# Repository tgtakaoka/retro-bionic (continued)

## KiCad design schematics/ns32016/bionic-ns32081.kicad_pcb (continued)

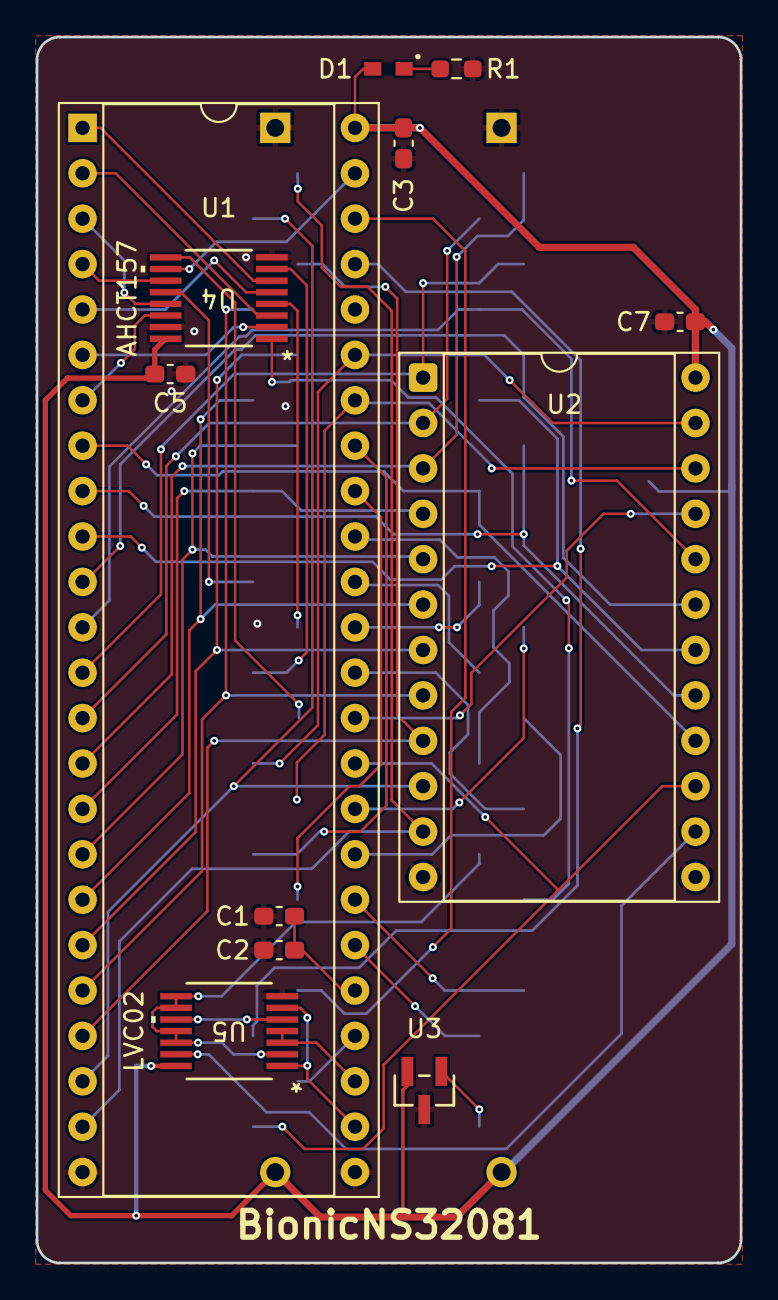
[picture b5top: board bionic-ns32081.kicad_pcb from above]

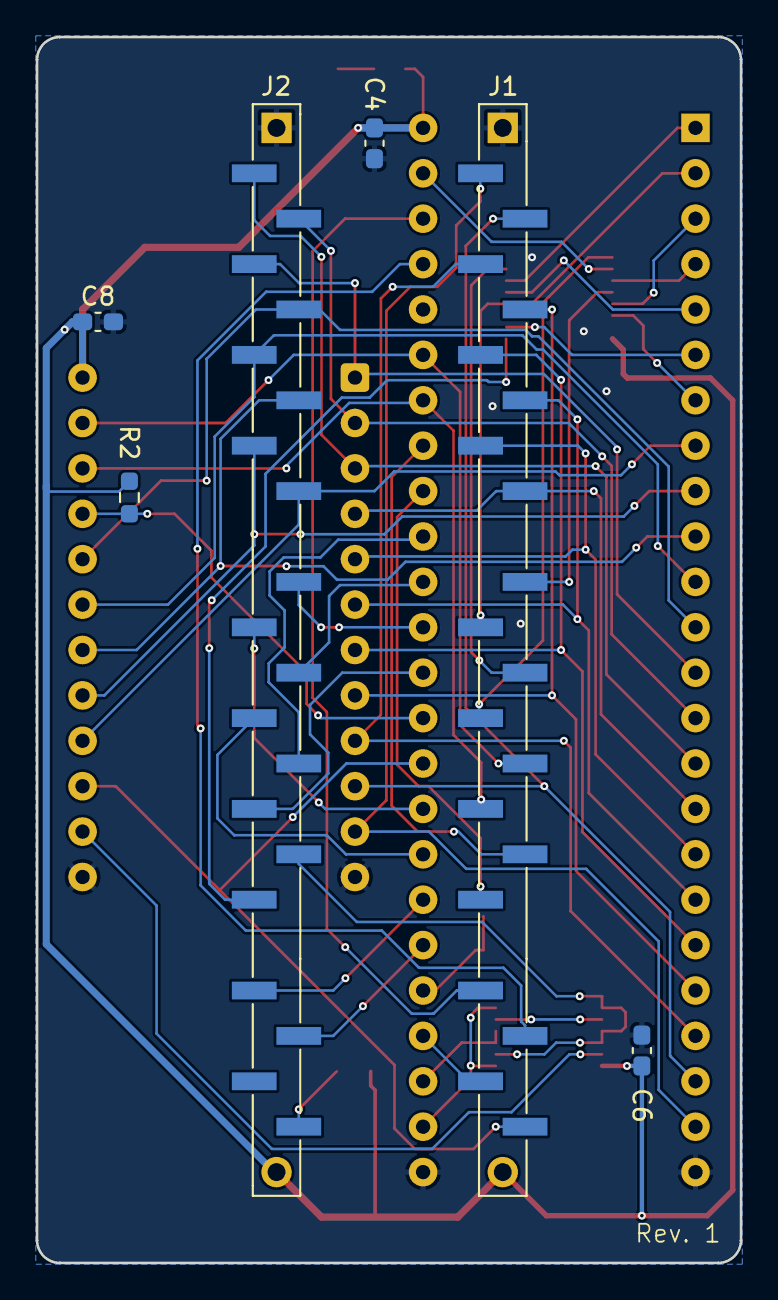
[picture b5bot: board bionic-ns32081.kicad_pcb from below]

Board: 2 copper layers, 39.4 x 68.6 mm, 18 parts (6 on the bottom side), 56 nets.

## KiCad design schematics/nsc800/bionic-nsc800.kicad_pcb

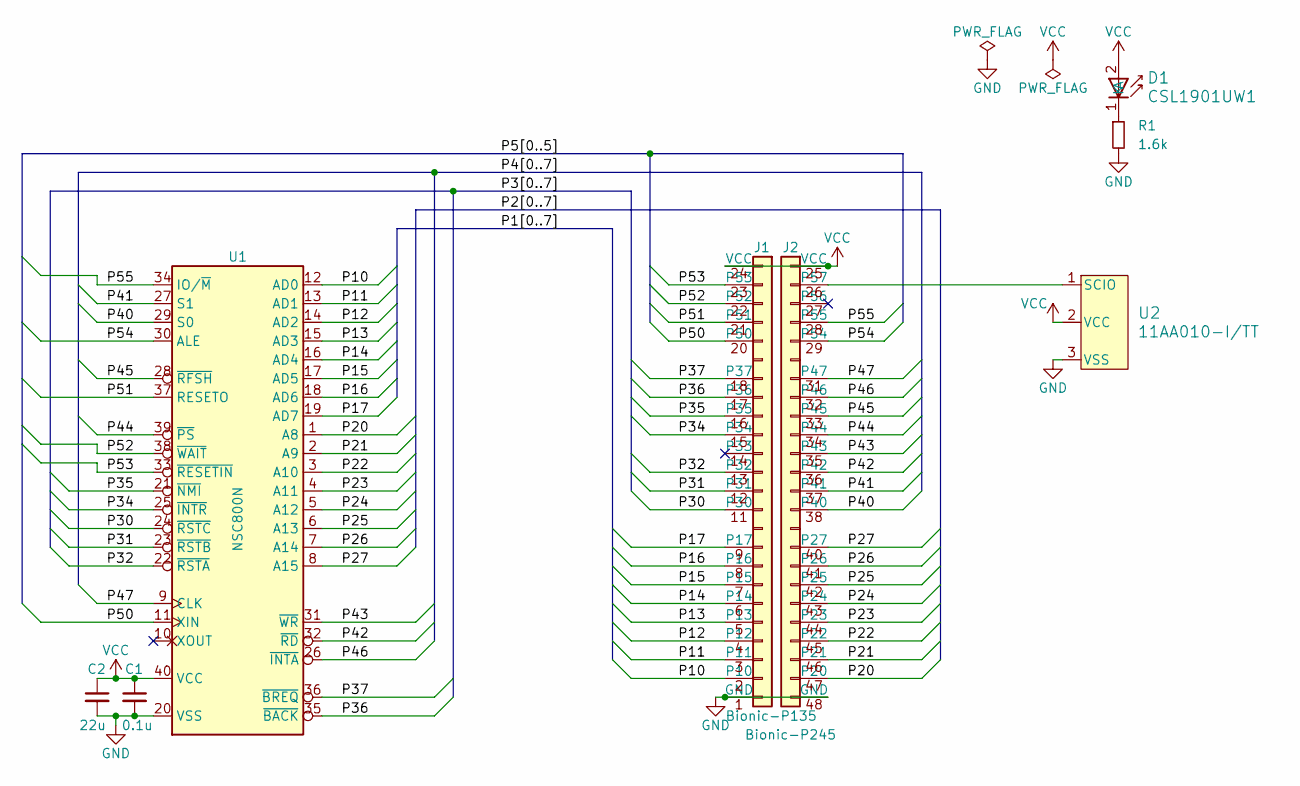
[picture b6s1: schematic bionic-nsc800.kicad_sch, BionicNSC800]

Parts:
C1: 0.1u; C_0603_1608Metric_Pad1.08x0.95mm_HandSolder
C2: 22u; C_0603_1608Metric_Pad1.08x0.95mm_HandSolder
D1: CSL1901UW1; LED_CSL1901UW1_ROM-M
J1: Bionic-P135; Bionic-P135_THT
J2: Bionic-P245; Bionic-P245_THT
R1: 1.6k; R_0603_1608Metric_Pad0.98x0.95mm_HandSolder
U1: NSC800N; DIP-40_W15.24mm_Socket
U2: 11AA010-I/TT; SOT-23_MC_MCH-M

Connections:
/P10: J1.2 (P10), U1.12 (AD0)
/P11: J1.3 (P11), U1.13 (AD1)
/P12: J1.4 (P12), U1.14 (AD2)
/P13: J1.5 (P13), U1.15 (AD3)
/P14: J1.6 (P14), U1.16 (AD4)
/P15: J1.7 (P15), U1.17 (AD5)
/P16: J1.8 (P16), U1.18 (AD6)
/P17: J1.9 (P17), U1.19 (AD7)
/P20: J2.47 (P20), U1.1 (A8)
/P21: J2.46 (P21), U1.2 (A9)
/P22: J2.45 (P22), U1.3 (A10)
/P23: J2.44 (P23), U1.4 (A11)
/P24: J2.43 (P24), U1.5 (A12)
/P25: J2.42 (P25), U1.6 (A13)
/P26: J2.41 (P26), U1.7 (A14)
/P27: J2.40 (P27), U1.8 (A15)
/P30: J1.11 (P30), U1.24 (~RSTC)
/P31: J1.12 (P31), U1.23 (~RSTB)
/P32: J1.13 (P32), U1.22 (~RSTA)
/P34: J1.15 (P34), U1.25 (~INTR)
/P35: J1.16 (P35), U1.21 (~NMI)
/P36: J1.17 (P36), U1.35 (~BACK)
/P37: J1.18 (P37), U1.36 (~BREQ)
/P40: J2.38 (P40), U1.29 (S0)
/P41: J2.37 (P41), U1.27 (S1)
/P42: J2.36 (P42), U1.32 (~RD)
/P43: J2.35 (P43), U1.31 (~WR)
/P44: J2.34 (P44), U1.39 (~PS)
/P45: J2.33 (P45), U1.28 (~RFSH)
/P46: J2.32 (P46), U1.26 (~INTA)
/P47: J2.31 (P47), U1.9 (CLK)
/P50: J1.20 (P50), U1.11 (XIN)
/P51: J1.21 (P51), U1.37 (RESETO)
/P52: J1.22 (P52), U1.38 (~WAIT)
/P53: J1.23 (P53), U1.33 (~RESETIN)
/P54: J2.29 (P54), U1.30 (ALE)
/P55: J2.28 (P55), U1.34 (IO/~M)
GND: C1.2, C2.2, J1.1 (GND), J2.48 (GND), R1.2, U1.20 (VSS), U2.3 (VSS)
unnamed: D1.1 (K), R1.1
unnamed: J2.26 (P57), U2.1 (SCIO)
VCC: C1.1, C2.1, D1.2 (A), J1.24 (VCC), J2.25 (VCC), U1.40 (VCC), U2.2 (VCC)

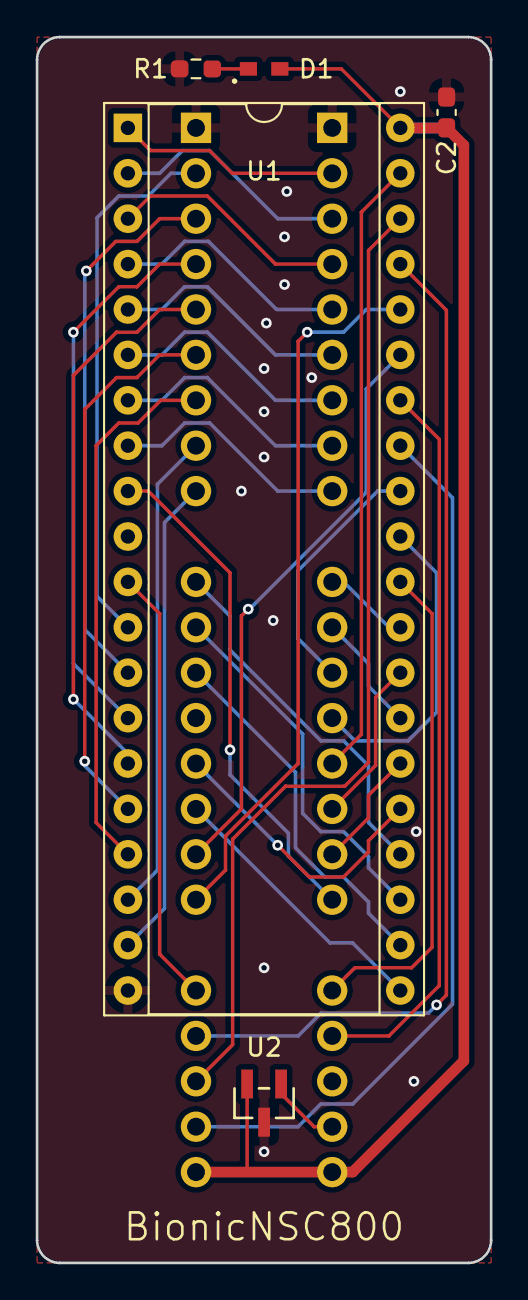
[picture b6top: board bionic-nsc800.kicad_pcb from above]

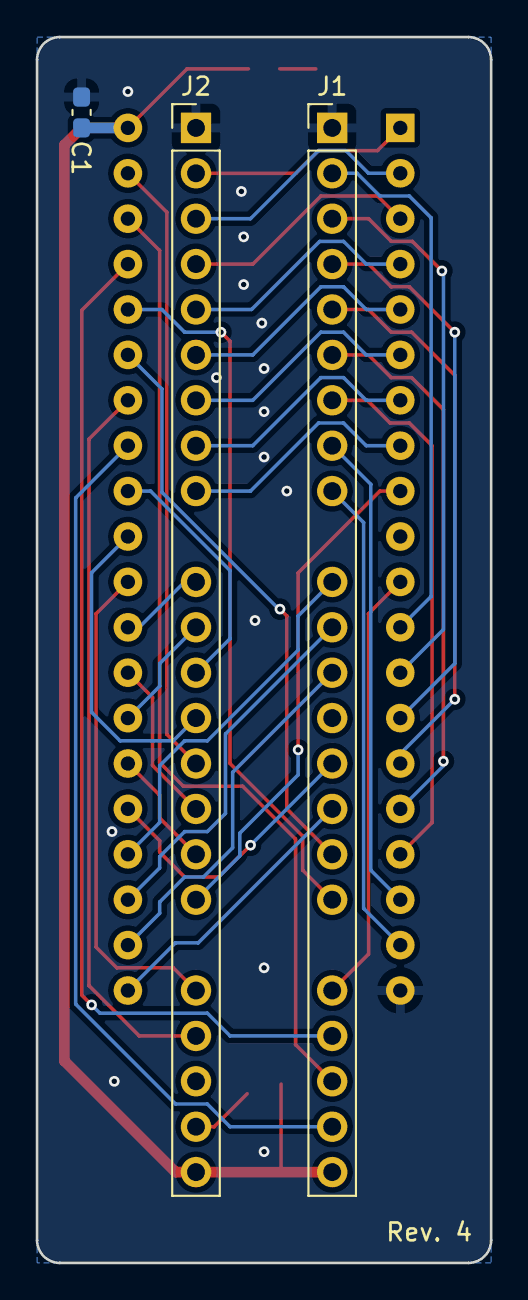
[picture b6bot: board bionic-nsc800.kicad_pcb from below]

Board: 2 copper layers, 25.4 x 68.6 mm, 8 parts (3 on the bottom side), 41 nets.

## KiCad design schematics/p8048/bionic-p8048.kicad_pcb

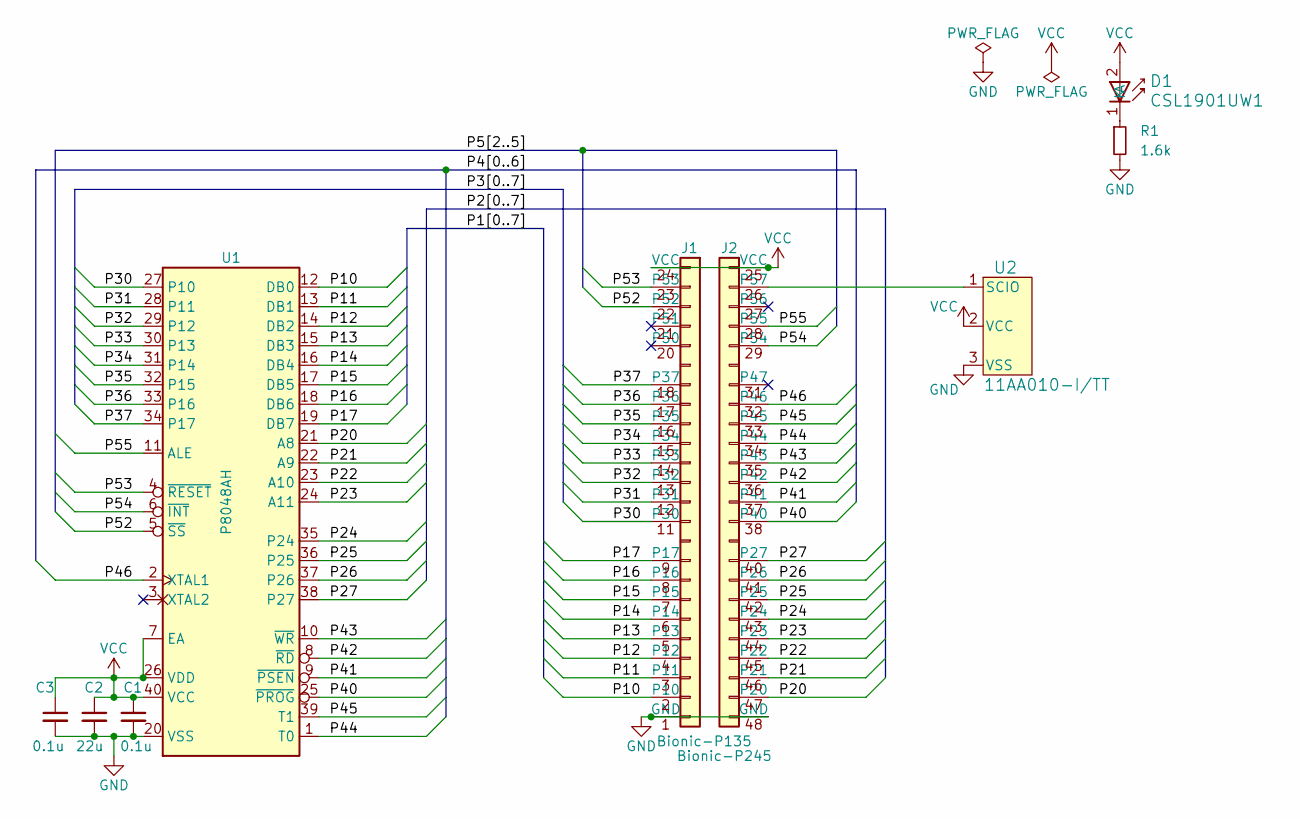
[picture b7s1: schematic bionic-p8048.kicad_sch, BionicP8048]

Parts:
C1, C3: 0.1u; C_0603_1608Metric_Pad1.08x0.95mm_HandSolder
C2: 22u; C_0603_1608Metric_Pad1.08x0.95mm_HandSolder
D1: CSL1901UW1; LED_CSL1901UW1_ROM-M
J1: Bionic-P135; Bionic-P135_THT
J2: Bionic-P245; Bionic-P245_THT
R1: 1.6k; R_0603_1608Metric_Pad0.98x0.95mm_HandSolder
U1: P8048AH; DIP-40_W15.24mm_Socket
U2: 11AA010-I/TT; SOT-23_MC_MCH-M

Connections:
/P10: J1.2 (P10), U1.12 (DB0)
/P11: J1.3 (P11), U1.13 (DB1)
/P12: J1.4 (P12), U1.14 (DB2)
/P13: J1.5 (P13), U1.15 (DB3)
/P14: J1.6 (P14), U1.16 (DB4)
/P15: J1.7 (P15), U1.17 (DB5)
/P16: J1.8 (P16), U1.18 (DB6)
/P17: J1.9 (P17), U1.19 (DB7)
/P20: J2.47 (P20), U1.21 (A8)
/P21: J2.46 (P21), U1.22 (A9)
/P22: J2.45 (P22), U1.23 (A10)
/P23: J2.44 (P23), U1.24 (A11)
/P24: J2.43 (P24), U1.35 (P24)
/P25: J2.42 (P25), U1.36 (P25)
/P26: J2.41 (P26), U1.37 (P26)
/P27: J2.40 (P27), U1.38 (P27)
/P30: J1.11 (P30), U1.27 (P10)
/P31: J1.12 (P31), U1.28 (P11)
/P32: J1.13 (P32), U1.29 (P12)
/P33: J1.14 (P33), U1.30 (P13)
/P34: J1.15 (P34), U1.31 (P14)
/P35: J1.16 (P35), U1.32 (P15)
/P36: J1.17 (P36), U1.33 (P16)
/P37: J1.18 (P37), U1.34 (P17)
/P40: J2.38 (P40), U1.25 (~PROG)
/P41: J2.37 (P41), U1.9 (~PSEN)
/P42: J2.36 (P42), U1.8 (~RD)
/P43: J2.35 (P43), U1.10 (~WR)
/P44: J2.34 (P44), U1.1 (T0)
/P45: J2.33 (P45), U1.39 (T1)
/P46: J2.32 (P46), U1.2 (XTAL1)
/P52: J1.22 (P52), U1.5 (~SS)
/P53: J1.23 (P53), U1.4 (~RESET)
/P54: J2.29 (P54), U1.6 (~INT)
/P55: J2.28 (P55), U1.11 (ALE)
GND: C1.2, C2.2, C3.2, J1.1 (GND), J2.48 (GND), R1.2, U1.20 (VSS), U2.3 (VSS)
unnamed: D1.1 (K), R1.1
unnamed: J2.26 (P57), U2.1 (SCIO)
VCC: C1.1, C2.1, C3.1, D1.2 (A), J1.24 (VCC), J2.25 (VCC), U1.7 (EA), U1.26 (VDD), U1.40 (VCC), U2.2 (VCC)

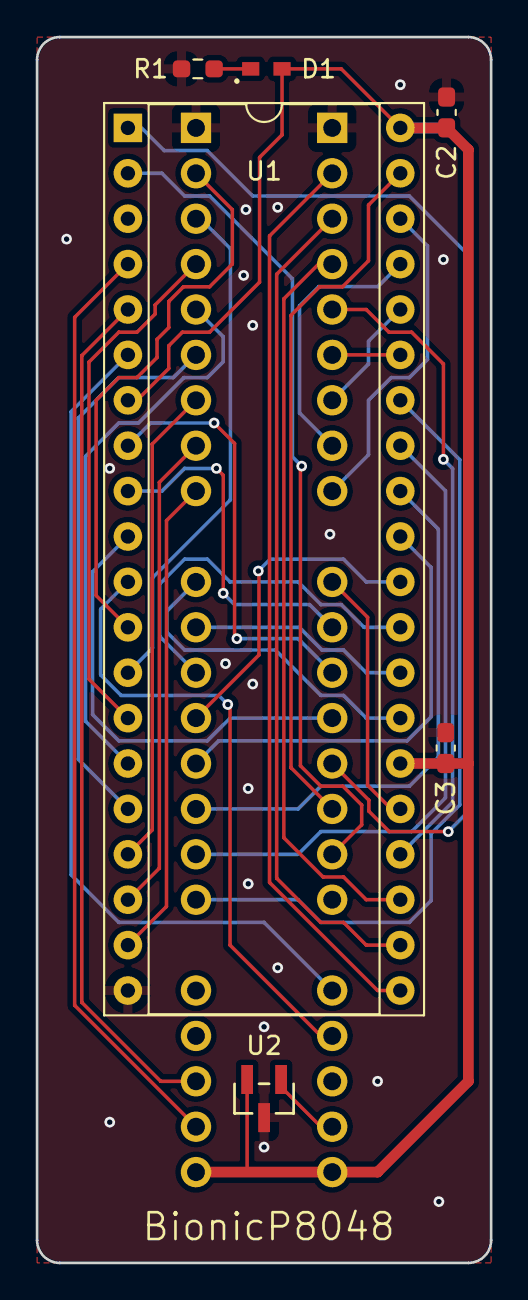
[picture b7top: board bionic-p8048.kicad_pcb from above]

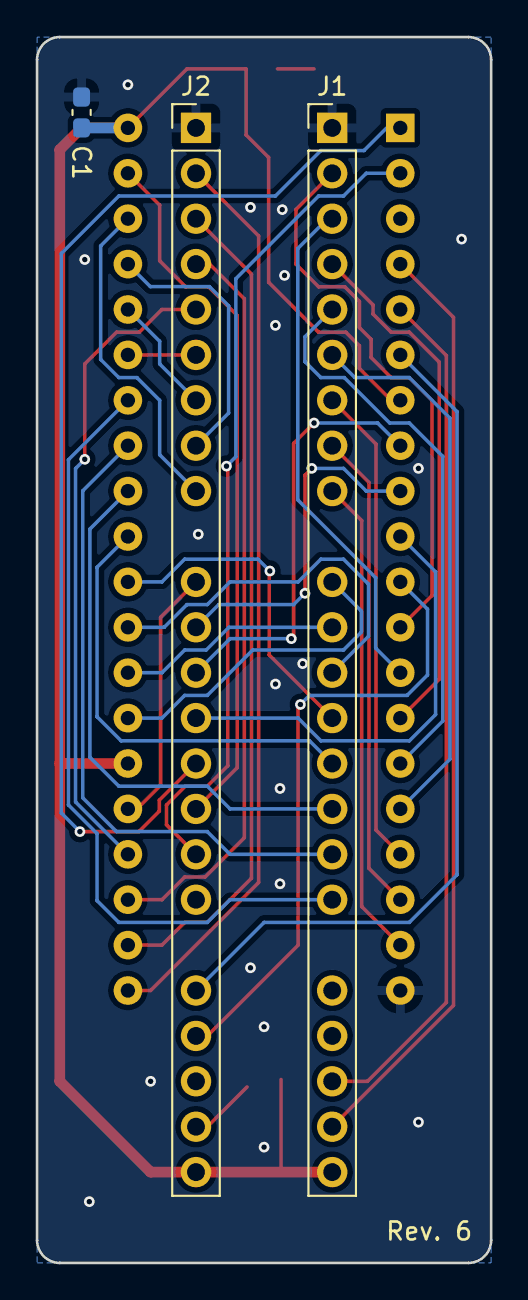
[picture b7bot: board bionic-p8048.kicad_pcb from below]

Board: 2 copper layers, 25.4 x 68.6 mm, 9 parts (3 on the bottom side), 39 nets.

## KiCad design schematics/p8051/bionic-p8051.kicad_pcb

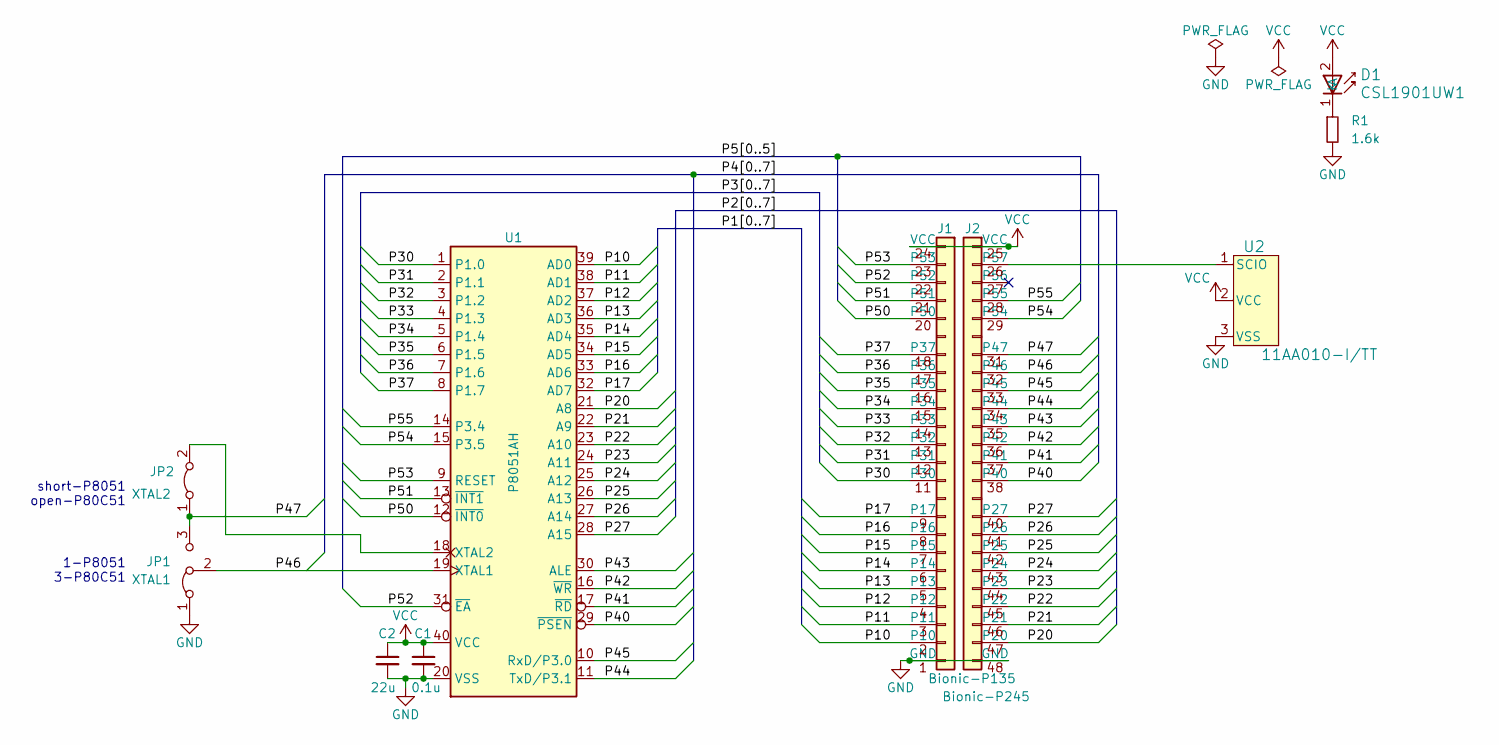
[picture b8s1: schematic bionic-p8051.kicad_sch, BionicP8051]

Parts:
C1: 0.1u; R_0603_1608Metric_Pad0.98x0.95mm_HandSolder
C2: 22u; R_0603_1608Metric_Pad0.98x0.95mm_HandSolder
D1: CSL1901UW1; LED_CSL1901UW1_ROM-M
J1: Bionic-P135; Bionic-P135_THT
J2: Bionic-P245; Bionic-P245_THT
JP1: XTAL1; SolderJumper-3_P1.3mm_Open_RoundedPad1.0x1.5mm_NumberLabels
JP2: XTAL2; SolderJumper-2_P1.3mm_Open_RoundedPad1.0x1.5mm
R1: 1.6k; R_0603_1608Metric_Pad0.98x0.95mm_HandSolder
U1: P8051AH; DIP-40_W15.24mm_Socket
U2: 11AA010-I/TT; SOT-23_MC_MCH-M

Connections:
/P10: J1.2 (P10), U1.39 (AD0)
/P11: J1.3 (P11), U1.38 (AD1)
/P12: J1.4 (P12), U1.37 (AD2)
/P13: J1.5 (P13), U1.36 (AD3)
/P14: J1.6 (P14), U1.35 (AD4)
/P15: J1.7 (P15), U1.34 (AD5)
/P16: J1.8 (P16), U1.33 (AD6)
/P17: J1.9 (P17), U1.32 (AD7)
/P20: J2.47 (P20), U1.21 (A8)
/P21: J2.46 (P21), U1.22 (A9)
/P22: J2.45 (P22), U1.23 (A10)
/P23: J2.44 (P23), U1.24 (A11)
/P24: J2.43 (P24), U1.25 (A12)
/P25: J2.42 (P25), U1.26 (A13)
/P26: J2.41 (P26), U1.27 (A14)
/P27: J2.40 (P27), U1.28 (A15)
/P30: J1.11 (P30), U1.1 (P1.0)
/P31: J1.12 (P31), U1.2 (P1.1)
/P32: J1.13 (P32), U1.3 (P1.2)
/P33: J1.14 (P33), U1.4 (P1.3)
/P34: J1.15 (P34), U1.5 (P1.4)
/P35: J1.16 (P35), U1.6 (P1.5)
/P36: J1.17 (P36), U1.7 (P1.6)
/P37: J1.18 (P37), U1.8 (P1.7)
/P40: J2.38 (P40), U1.29 (~PSEN)
/P41: J2.37 (P41), U1.17 (~RD)
/P42: J2.36 (P42), U1.16 (~WR)
/P43: J2.35 (P43), U1.30 (ALE)
/P44: J2.34 (P44), U1.11 (TxD/P3.1)
/P45: J2.33 (P45), U1.10 (RxD/P3.0)
/P46: J2.32 (P46), JP1.2 (C), U1.19 (XTAL1)
/P47: J2.31 (P47), JP1.3 (B), JP2.1 (A)
/P50: J1.20 (P50), U1.12 (~INT0)
/P51: J1.21 (P51), U1.13 (~INT1)
/P52: J1.22 (P52), U1.31 (~EA)
/P53: J1.23 (P53), U1.9 (RESET)
/P54: J2.29 (P54), U1.15 (P3.5)
/P55: J2.28 (P55), U1.14 (P3.4)
GND: C1.2, C2.2, J1.1 (GND), J2.48 (GND), JP1.1 (A), R1.2, U1.20 (VSS), U2.3 (VSS)
unnamed: D1.1 (K), R1.1
unnamed: J2.26 (P57), U2.1 (SCIO)
unnamed: JP2.2 (B), U1.18 (XTAL2)
VCC: C1.1, C2.1, D1.2 (A), J1.24 (VCC), J2.25 (VCC), U1.40 (VCC), U2.2 (VCC)

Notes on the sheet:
short-P8051 open-P80C51
1-P8051 3-P80C51

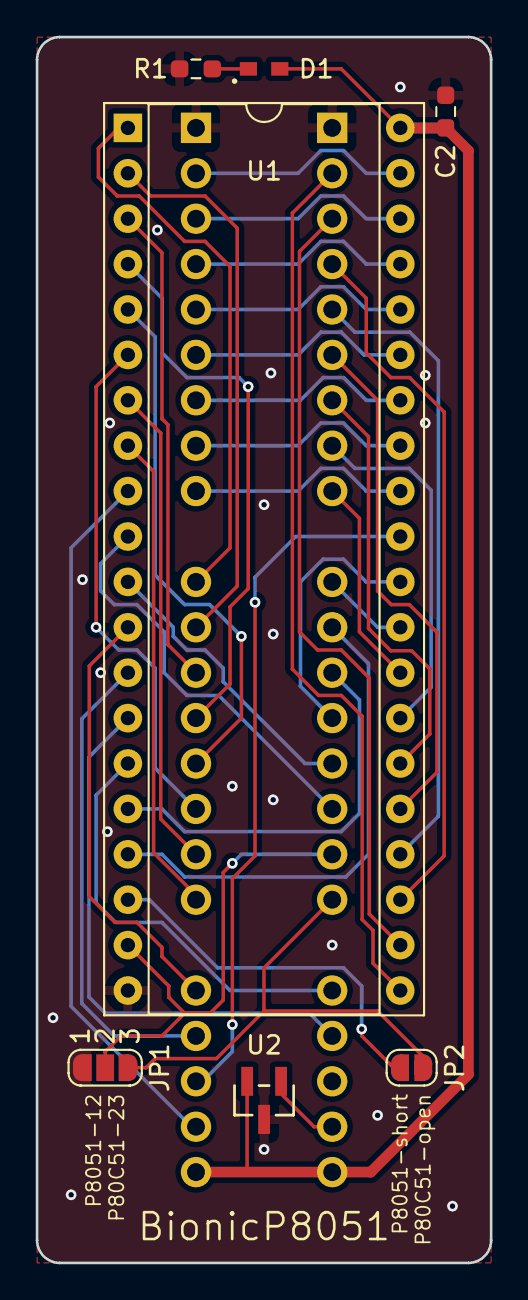
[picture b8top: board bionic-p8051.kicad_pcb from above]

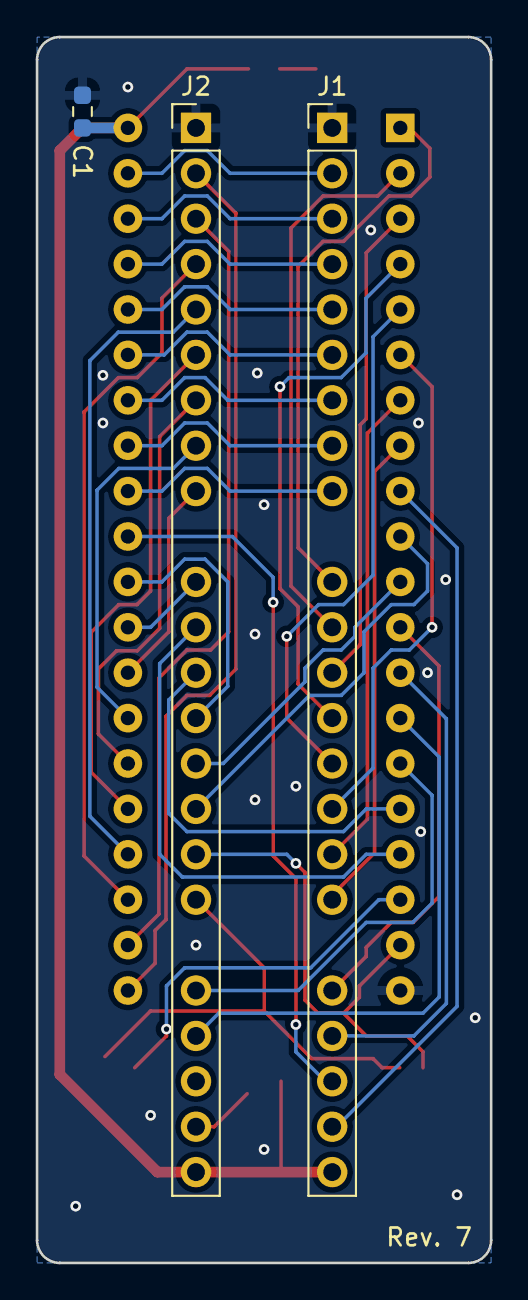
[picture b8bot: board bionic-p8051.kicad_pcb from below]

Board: 2 copper layers, 25.4 x 68.6 mm, 10 parts (3 on the bottom side), 43 nets.
